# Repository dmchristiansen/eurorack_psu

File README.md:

# eurorack_psu

This is a simple power supply board for a eurorack setup.

The PSU takes 12VAC input and provides +/-12V and 5V DC.
The plug, switch, and indicator leds are off-board (either a panel or case)

The bus board is supplied by the spade connectors from the PSU and provides multiple 16-pin headers.
(http://www.doepfer.de/a100_man/a100t_e.htm)

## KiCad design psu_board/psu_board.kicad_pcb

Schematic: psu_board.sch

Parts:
C1, C2, C7, C8: 4700uF; CP_Radial_D18.0mm_P7.50mm
C3, C4, C5, C6, C9, C10: 1uF; CP_Radial_D5.0mm_P2.00mm
D1, D2, D4, D5, D7, D8, D9, D11: 1N4004; D_DO-35_SOD27_P10.16mm_Horizontal
D3, D6, D10: LED; LED_D3.0mm
F1: Fuse; Fuseholder5x20_horiz_SemiClosed_Casing10x25mm
J1: 12VAC_INPUT; spade_connector
J2: +5V; spade_connector
J3: +12V; spade_connector
J4: GND; spade_connector
J5: -12V; spade_connector
J6: GND_INPUT; spade_connector
R1, R3: 1k; R_Axial_DIN0207_L6.3mm_D2.5mm_P10.16mm_Horizontal
R2: 330; R_Axial_DIN0207_L6.3mm_D2.5mm_P10.16mm_Horizontal
U1: LM7812_TO220; TO-220-3_Vertical
U2: LM7805_TO220; TO-220-3_Vertical
U3: LM7912_TO220; TO-220-3_Vertical

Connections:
+5V: C6.1, D5.2 (A), D6.2, D7.1 (K), J2.1, J2.2, U2.3
+12V: C4.1, D1.2 (A), D3.2, D4.1 (K), J3.1, J3.2, U1.3 (VO)
+12VA: F1.2, J1.1, J1.2
-12V: C10.2, D8.1 (K), D10.1, D11.2 (A), J5.1, J5.2, U3.3 (VO)
GND: C1.2, C2.2, C3.2, C4.2, C5.2, C6.2, C7.1, C8.1, C9.1, C10.1, D4.2 (A), D7.2 (A), D11.1 (K), J4.1, J4.2, J6.1, J6.2, R1.2, R2.2, R3.2, U1.2 (GND), U2.2, U3.1 (GND)
unnamed: C1.1, C2.1, C3.1, C5.1, D1.1 (K), D2.1 (K), D5.1 (K), U1.1 (VI), U2.1
unnamed: C7.2, C8.2, C9.2, D8.2 (A), D9.2 (A), U3.2 (VI)
unnamed: D2.2 (A), D9.1 (K), F1.1
unnamed: D3.1, R1.1
unnamed: D6.1, R2.1
unnamed: D10.2, R3.1

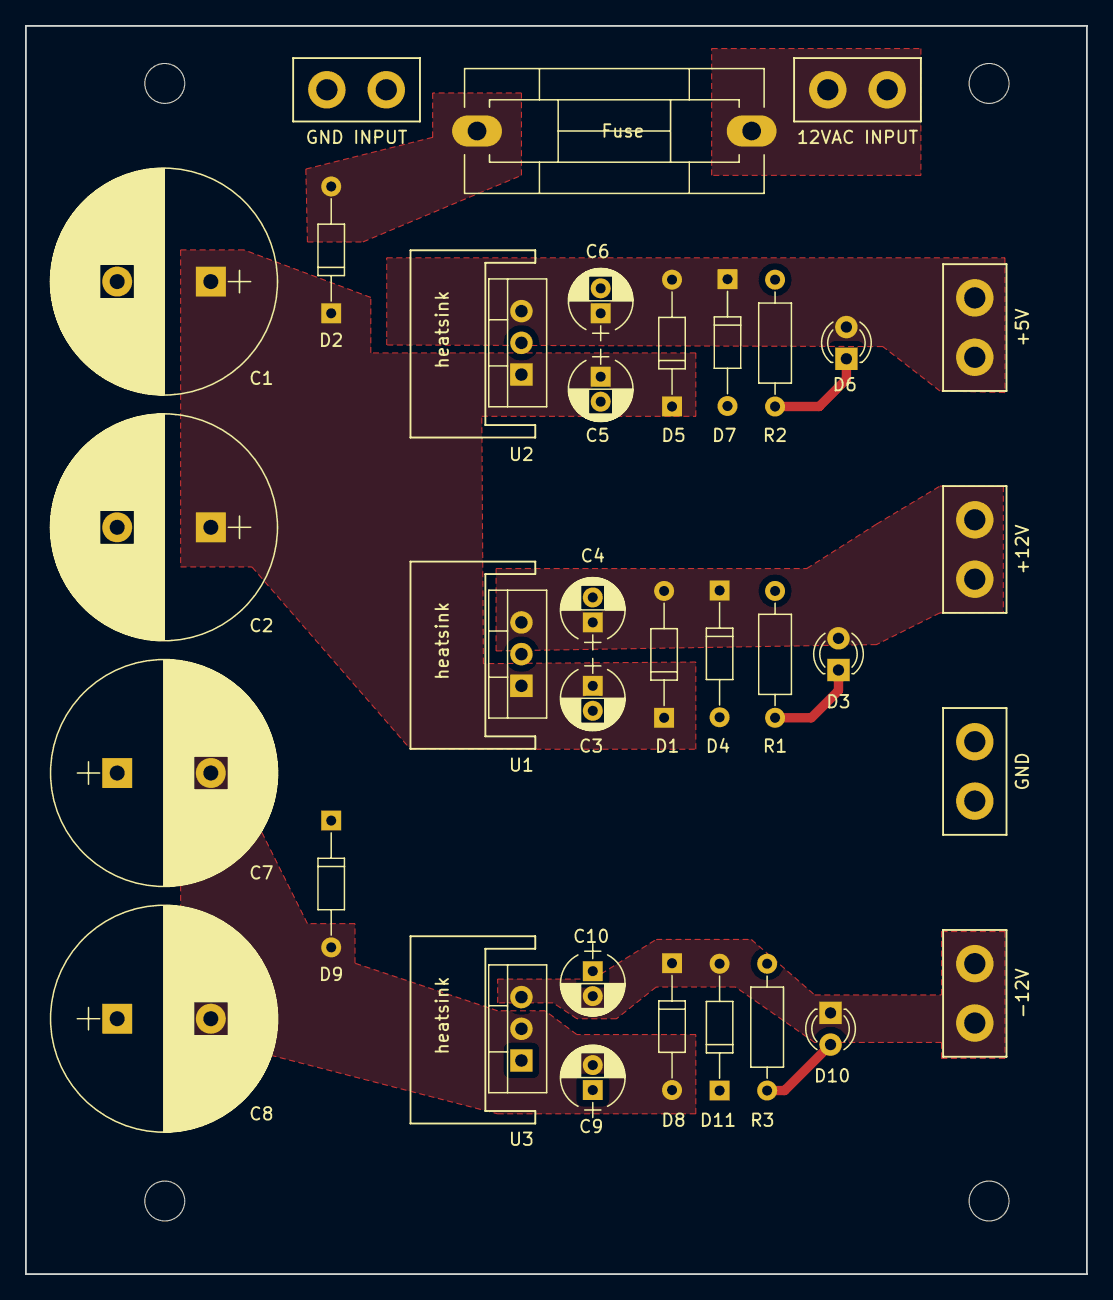
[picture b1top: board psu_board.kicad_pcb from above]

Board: 2 copper layers, 85.0 x 100.0 mm, 37 parts (0 on the bottom side), 11 nets.

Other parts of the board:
heatsink: heatsink_25mm_10mm
heatsink#2, heatsink#3: heatsink_25mm_10mm

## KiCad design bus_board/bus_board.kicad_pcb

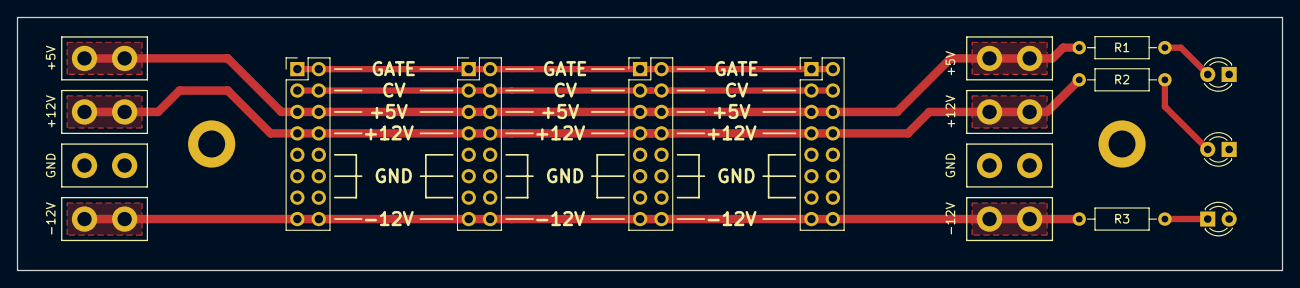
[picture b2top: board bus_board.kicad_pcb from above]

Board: 2 copper layers, 150.0 x 30.0 mm, 18 parts (0 on the bottom side), 9 nets.

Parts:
+5V, +5V#2: +5V; spade_connector
+12V, +12V#2: +12V; spade_connector
-12V, -12V#2: -12V; spade_connector
D1, D2, D3: LED; LED_D3.0mm
GND: GND; spade_connector
GND#2: GND; spade_connector
J5, J6, J7, J8: Conn_02x08_Odd_Even; Pin_Header_Straight_2x08_Pitch2.54mm
R1, R3: 2k; R_Axial_DIN0207_L6.3mm_D2.5mm_P10.16mm_Horizontal
R2: 1k; R_Axial_DIN0207_L6.3mm_D2.5mm_P10.16mm_Horizontal

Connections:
/+5V: +5V.1, +5V.2, +5V#2.1, +5V#2.2, J5.5, J5.6, J6.5, J6.6, J7.5, J7.6, J8.5, J8.6, R1.1
/+12V: +12V.1, +12V.2, +12V#2.1, +12V#2.2, J5.7, J5.8, J6.7, J6.8, J7.7, J7.8, J8.7, J8.8, R2.1
/-12V: -12V.1, -12V.2, -12V#2.1, -12V#2.2, J5.15, J5.16, J6.15, J6.16, J7.15, J7.16, J8.15, J8.16, R3.1
/CV: J5.3, J5.4, J6.3, J6.4, J7.3, J7.4, J8.3, J8.4
/GATE: J5.1, J5.2, J6.1, J6.2, J7.1, J7.2, J8.1, J8.2
/GND: D1.1, D2.1, D3.2, GND.1, GND.2, GND#2.1, GND#2.2, J5.9, J5.10, J5.11, J5.12, J5.13, J5.14, J6.9, J6.10, J6.11, J6.12, J6.13, J6.14, J7.9, J7.10, J7.11, J7.12, J7.13, J7.14, J8.9, J8.10, J8.11, J8.12, J8.13, J8.14
unnamed: D1.2, R1.2
unnamed: D2.2, R2.2
unnamed: D3.1, R3.2

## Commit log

2018-12-15 added fuse holder
2019-01-09 added gerbers
